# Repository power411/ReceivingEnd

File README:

Hello World!  This contains documentation, schematics and ideas for the Receiving end of our IR transmission device.

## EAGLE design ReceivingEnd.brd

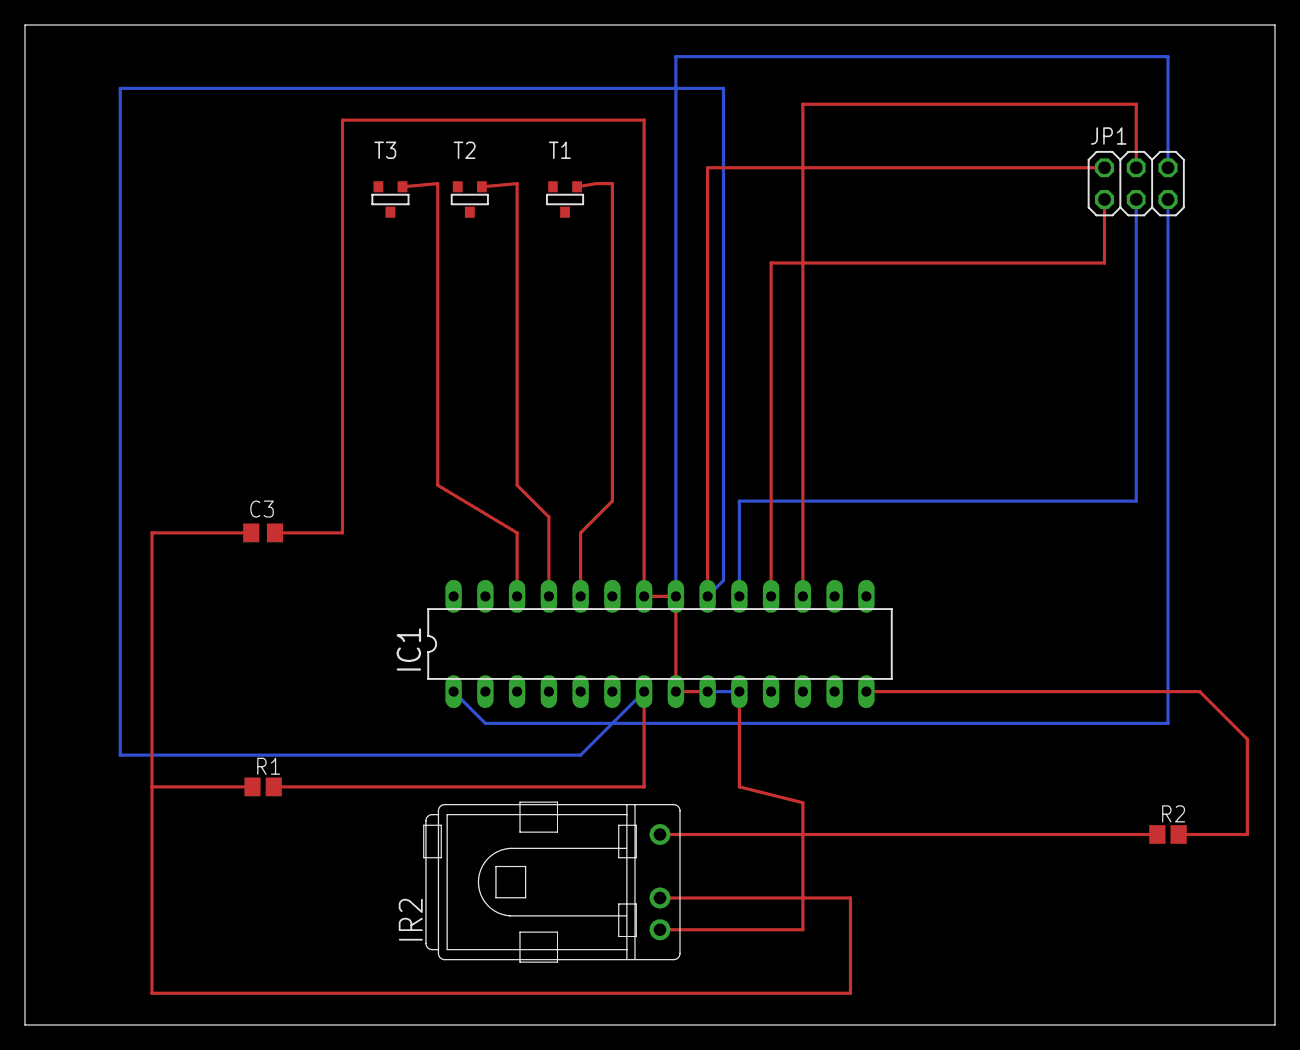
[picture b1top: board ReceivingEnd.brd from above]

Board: 2 copper layers, 100.0 x 80.0 mm, 9 parts (0 on the bottom side), 12 nets.

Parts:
C3: TBD; C0805
IC1: MEGA8-P; DIL28-3
IR2: TSOP1756TB1; TSOP17_TB1
JP1: 2X03
R1, R2: TBD; R0805
T1, T2, T3: SOT-23

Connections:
GND: C3.2, IC1.8, IC1.9, IC1.10, IC1.21, IC1.22, IR2.GND, JP1.6
unnamed: IR2.VO, R2.1
unnamed: IC1.26, T3.3
unnamed: IC1.25, T2.3
unnamed: IC1.24, T1.3
unnamed: C3.1, IR2.VS, R1.1
unnamed: IC1.14, R2.2
unnamed: IC1.17, JP1.4
unnamed: IC1.18, JP1.1
unnamed: IC1.19, JP1.3
unnamed: IC1.1, JP1.5
VCC: IC1.7, IC1.20, JP1.2, R1.2

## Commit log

2012-11-03 Commit #2
    Receiving End(2).sch is the most recent version of our schematic for the
    infrared receiving module of our device. readme file is a text file that
    was altered
2012-11-03 read me updated
2012-11-04 the initia PCB layout of the receiving end part
2012-11-04 polished schematic
2012-11-06 The Receiving End Layout before meeting with Greenberg
2012-11-06 eceiving end schematic before making the changes that Andrew suggested
2012-11-08 solomon
    uploaded with unfinished changes that andrew suggested. We still need an
    18 Volt to 5 Volt DC-DC converter.
